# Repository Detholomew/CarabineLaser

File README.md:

# CarabineLaser
Projet d'une carabine laser avec une cible pour biathlon.

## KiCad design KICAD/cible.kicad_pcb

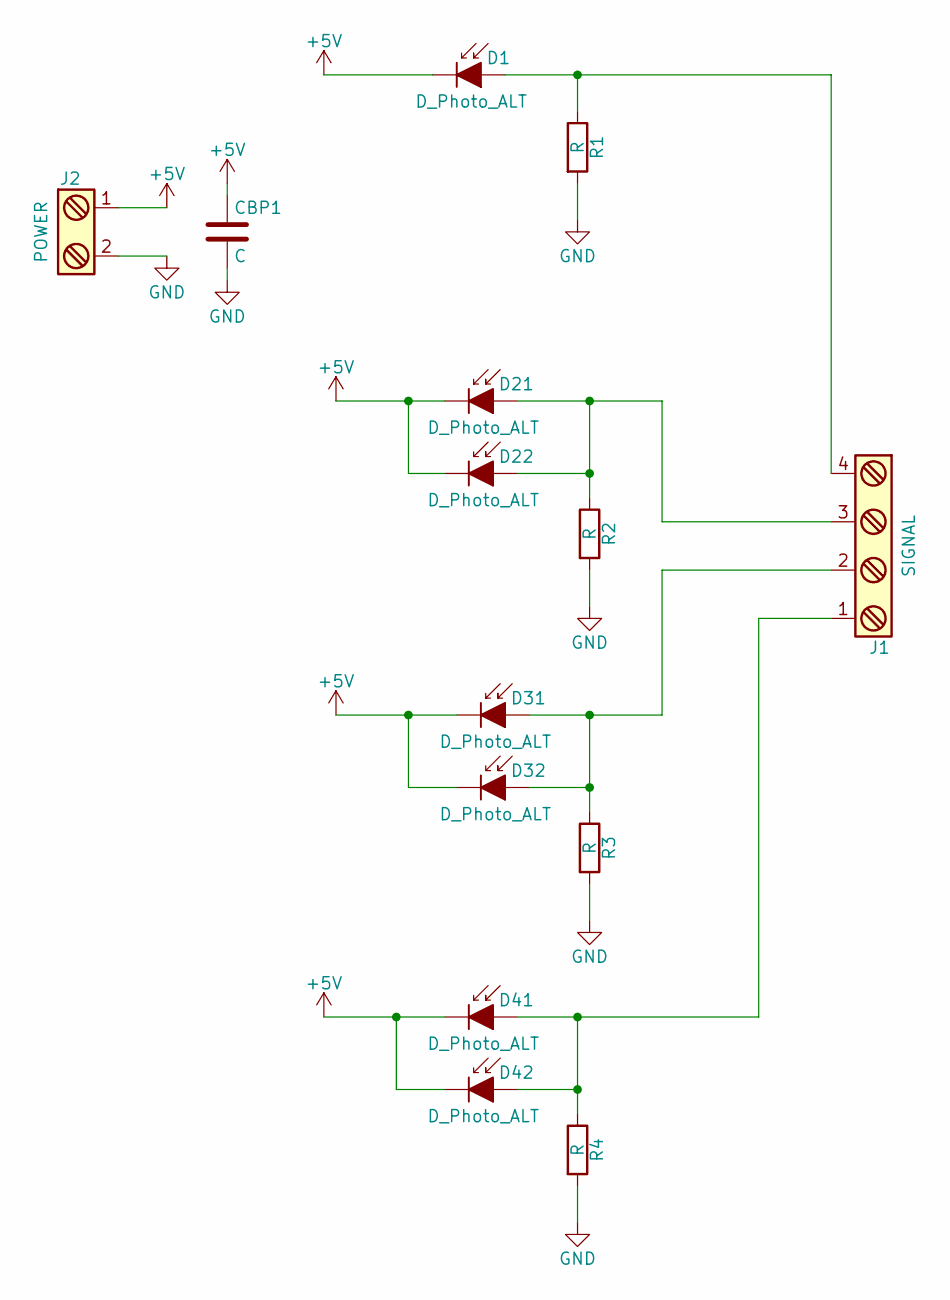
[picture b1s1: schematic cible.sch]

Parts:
CBP1: C; C_0805_HandSoldering
D1, D21, D22, D31, D32, D41, D42: D_Photo_ALT; LED_D5.0mm
J1: SIGNAL; Pin_Header_Straight_1x04_Pitch2.54mm
J2: POWER; Pin_Header_Straight_1x02_Pitch2.54mm
R1, R2, R3, R4: R; R_0805_HandSoldering

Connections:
+5V: CBP1.1, D1.1 (K), D21.1 (K), D22.1 (K), D31.1 (K), D32.1 (K), D41.1 (K), D42.1 (K), J2.1
GND: CBP1.2, J2.2, R1.2, R2.2, R3.2, R4.2
unnamed: D1.2 (A), J1.4, R1.1
unnamed: D21.2 (A), D22.2 (A), J1.3, R2.1
unnamed: D31.2 (A), D32.2 (A), J1.2, R3.1
unnamed: D41.2 (A), D42.2 (A), J1.1, R4.1

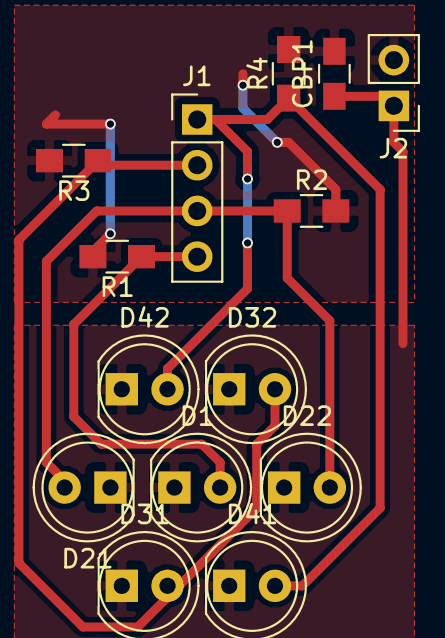
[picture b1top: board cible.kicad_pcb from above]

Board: 2 copper layers, 14 parts (0 on the bottom side), 6 nets.

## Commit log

2017-03-31 cible: arduino et design carte imprime
    programme de la cible et fichiers de la PCB de la cible
2017-03-31 Organisation and stable version of cible.ino
2017-04-03 First upload of Carabine, LCD and XBee
2017-04-25 New changes
2017-04-27 Version finale (ou presque de la carabine)
    Implémentation des affichages sur le LCD etc.. Manque uniquement le XBee
2017-04-27 Derniers changes a la cible et ajoute du rapport
2017-04-27 Clean up
